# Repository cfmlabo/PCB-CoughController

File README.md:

# カフコントローラ用基板

- カフスイッチ(Switch + LED)最大５+２個  
  - J9は予備(SW6, SW7)なので実装しなくてよい
- オーディオリレー  
  - APSでは使用しないので実装しなくてよい
- GPIO(IN 8/OUT 8)  

[BOM](./BOM.md)

## CPI-DIO対応表

### Board1 / IN

| ピン番号 | 機能 |
| -- | -- |
| 1 | NC |
| 2 | SW 7 |
| 3 | SW 6 |
| 4 | SW 5 |
| 5 | SW 4 |
| 6 | SW 3 |
| 7 | SW 2 |
| 8 | SW 1 |

### Board1 / OUT

| ピン番号 | 機能 |
| -- | -- |
| 1 | リレー |
| 2 | SW 7 |
| 3 | SW 6 |
| 4 | SW 5 |
| 5 | SW 4 |
| 6 | SW 3 |
| 7 | SW 2 |
| 8 | SW 1 |

### Board2 / IN

| ピン番号 | 機能 |
| -- | -- |
| 1 | IN 8 |
| 2 | IN 7 |
| 3 | IN 6 |
| 4 | IN 5 |
| 5 | IN 4 |
| 6 | IN 3 |
| 7 | IN 2 |
| 8 | IN 1 |

### Board2 / OUT

| ピン番号 | 機能 |
| -- | -- |
| 1 | OUT 8 |
| 2 | OUT 7 |
| 3 | OUT 6 |
| 4 | OUT 5 |
| 5 | OUT 4 |
| 6 | OUT 3 |
| 7 | OUT 2 |
| 8 | OUT 1 |

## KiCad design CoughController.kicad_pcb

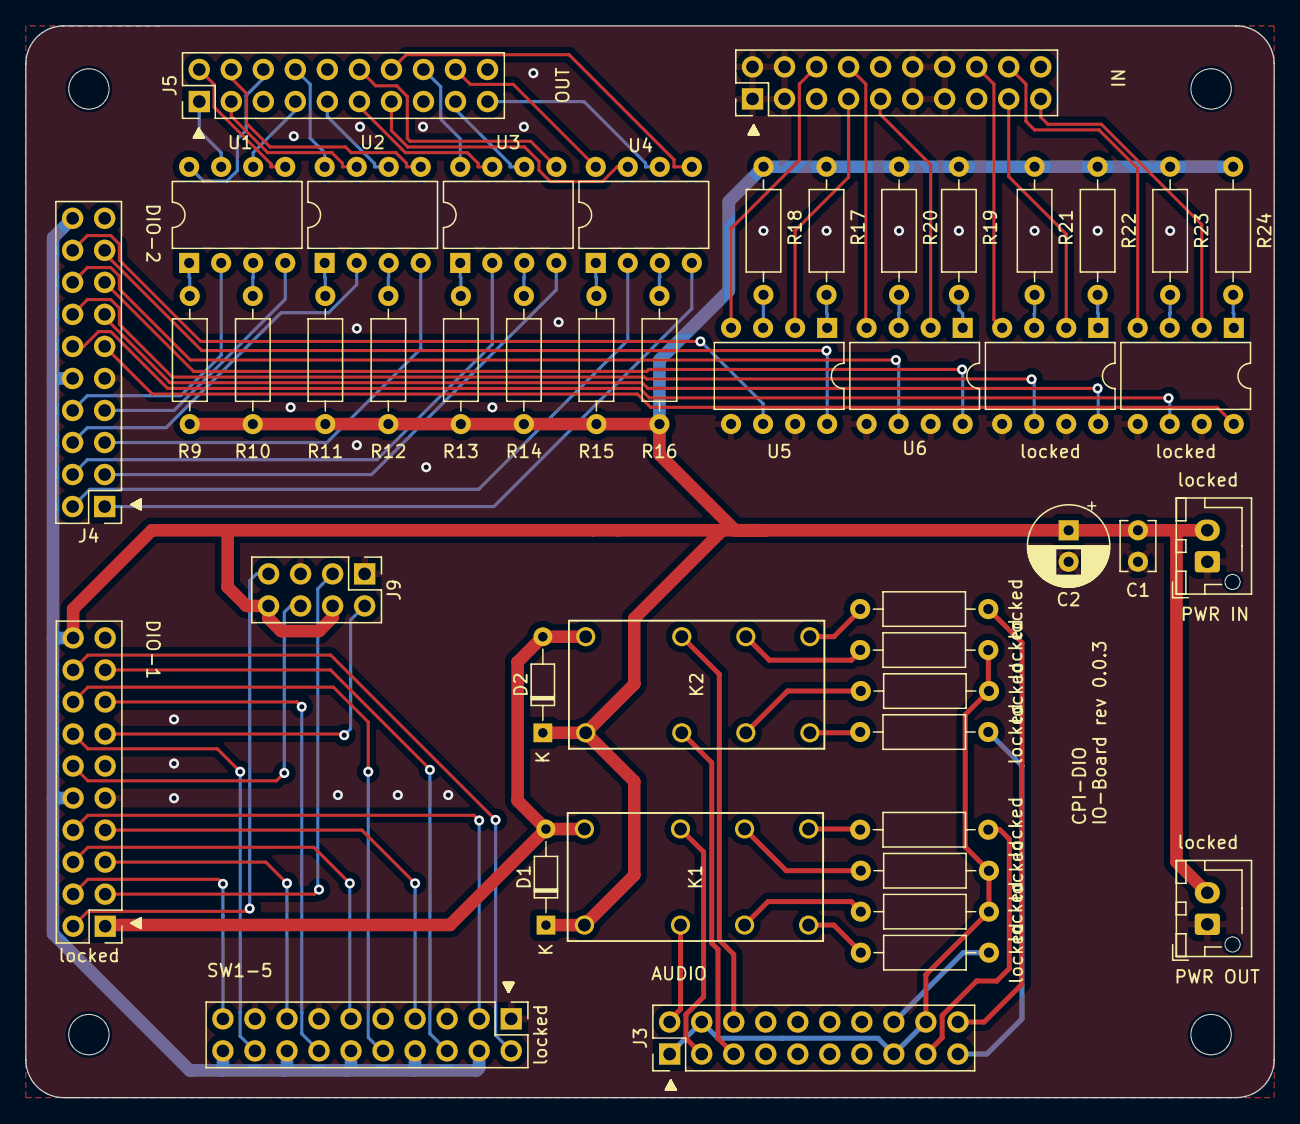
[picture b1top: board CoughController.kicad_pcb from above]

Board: 2 copper layers, 99.0 x 85.0 mm, 51 parts (0 on the bottom side), 90 nets.

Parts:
C1: 0.1uF; C_Disc_D3.8mm_W2.6mm_P2.50mm
C2: 100uF/25V; CP_Radial_D6.3mm_P2.50mm
D1, D2: 1S1588; D_DO-34_SOD68_P7.62mm_Horizontal
H1, H2, H3, H4: MountingHole; MountingHole_3.2mm_M3
J3: AUDIO IN/OUT; BoxHeader_2x10_P2.54mm_Vertical
J4: DIO-2; BoxHeader_2x10_P2.54mm_Vertical
J5: GPIO-OUT; BoxHeader_2x10_P2.54mm_Vertical
J6: GPIO-IN; BoxHeader_2x10_P2.54mm_Vertical
J9: Conn_02x04_Odd_Even; PinHeader_2x04_P2.54mm_Vertical
K1, K2: G6A-274P-DC5; RELAY_G6A-274P-DC5
R9, R10, R11, R12, R13, R14, R15, R16, R17, R18, R19, R20, R21, R22, R23, R24: 510; R_Axial_DIN0207_L6.3mm_D2.5mm_P10.16mm_Horizontal
U1, U2, U3, U4, U5, U6: TLP627-2; DIP-8_W7.62mm
locked: SW1-5; BoxHeader_2x10_P2.54mm_Vertical
locked#2, locked#7: TLP627-2; DIP-8_W7.62mm
locked#3, locked#4, locked#9, locked#10: 10K; R_Axial_DIN0207_L6.3mm_D2.5mm_P10.16mm_Horizontal
locked#5, locked#12, locked#13, locked#14: 220; R_Axial_DIN0207_L6.3mm_D2.5mm_P10.16mm_Horizontal
locked#6: DIO-1; BoxHeader_2x10_P2.54mm_Vertical
locked#8: PWR_IN; JST_XH_B2B-XH-AM_1x02_P2.50mm_Vertical
locked#11: PWR_OUT; JST_XH_B2B-XH-AM_1x02_P2.50mm_Vertical

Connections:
AUDIO-IN-L-COLD: J3.3, K1.13
AUDIO-IN-L-GND: J3.1, J3.4, J3.15, J3.18, locked#3.2, locked#4.2, locked#9.1, locked#10.1
AUDIO-IN-L-HOT: J3.2, K1.4
AUDIO-IN-R-COLD: J3.6, K2.13
AUDIO-IN-R-HOT: J3.5, K2.4
AUDIO-OUT-L-COLD: J3.17, locked#14.1
AUDIO-OUT-L-HOT: J3.16, locked#13.2
AUDIO-OUT-R-COLD: J3.20, locked#5.2
AUDIO-OUT-R-HOT: J3.19, locked#12.1
COM0: C1.1, C2.1, D1.1 (K), D2.1 (K), J4.10, J4.20, J9.4, J9.8, K1.1, K2.1, R9.2, R10.2, R11.2, R12.2, R13.2, R14.2, R15.2, R16.2, R17.2, R18.2, R19.2, R20.2, R21.2, R22.2, R23.2, R24.2, locked.4, locked.8, locked.12, locked.16, locked.20, locked#6.10, locked#6.20, locked#8.2, locked#11.2
DIO-2/IN1: J4.18, U5.6
DIO-2/IN2: J4.17, U5.8
DIO-2/IN3: J4.16, U6.6
DIO-2/IN4: J4.15, U6.8
DIO-2/IN5: J4.14, locked#7.6
DIO-2/IN6: J4.13, locked#7.8
DIO-2/IN7: J4.12, locked#2.6
DIO-2/IN8: J4.11, locked#2.8
DIO-2/OUT1: J4.8, U1.2
DIO-2/OUT2: J4.7, U1.4
DIO-2/OUT3: J4.6, U2.2
DIO-2/OUT4: J4.5, U2.4
DIO-2/OUT5: J4.4, U3.2
DIO-2/OUT6: J4.3, U3.4
DIO-2/OUT7: J4.2, U4.2
DIO-2/OUT8: J4.1, U4.4
GND: C1.2, C2.2, J4.9, J6.1, J6.2, J6.3, J6.4, J6.11, J6.12, J6.13, J6.14, J9.1, J9.5, U5.5, U5.7, U6.5, U6.7, locked.1, locked.5, locked.9, locked.13, locked.17, locked#2.5, locked#2.7, locked#6.9, locked#7.5, locked#7.7, locked#8.1, locked#11.1
GPIO-IN/1P: J6.6, U5.4
GPIO-IN/2P: J6.7, U5.2
GPIO-IN/3P: J6.8, U6.4
GPIO-IN/4P: J6.9, U6.2
GPIO-IN/5P: J6.16, locked#7.4
GPIO-IN/6P: J6.17, locked#7.2
GPIO-IN/7P: J6.18, locked#2.4
GPIO-IN/8P: J6.19, locked#2.2
GPIO-OUT/1M: J5.1, U1.7
GPIO-OUT/1P: J5.6, U1.8
GPIO-OUT/2M: J5.2, U1.5
GPIO-OUT/2P: J5.7, U1.6
GPIO-OUT/3M: J5.3, U2.7
GPIO-OUT/3P: J5.8, U2.8
GPIO-OUT/4M: J5.4, U2.5
GPIO-OUT/4P: J5.9, U2.6
GPIO-OUT/5M: J5.11, U3.7
GPIO-OUT/5P: J5.16, U3.8
GPIO-OUT/6M: J5.12, U3.5
GPIO-OUT/6P: J5.17, U3.6
GPIO-OUT/7M: J5.13, U4.7
GPIO-OUT/7P: J5.18, U4.8
GPIO-OUT/8M: J5.14, U4.5
GPIO-OUT/8P: J5.19, U4.6
unnamed: K1.6, locked#9.2
unnamed: K1.8, locked#13.1
unnamed: K1.9, locked#14.2
unnamed: K1.11, locked#3.1
unnamed: K2.6, locked#10.2
unnamed: K2.8, locked#12.2
unnamed: K2.9, locked#5.1
unnamed: K2.11, locked#4.1
unnamed: R9.1, U1.1
unnamed: R10.1, U1.3
unnamed: R11.1, U2.1
unnamed: R12.1, U2.3
unnamed: R13.1, U3.1
unnamed: R14.1, U3.3
unnamed: R15.1, U4.1
unnamed: R16.1, U4.3
unnamed: R17.1, U5.1
unnamed: R18.1, U5.3
unnamed: R19.1, U6.1
unnamed: R20.1, U6.3
unnamed: R21.1, locked#7.3
unnamed: R22.1, locked#7.1
unnamed: R23.1, locked#2.3
unnamed: R24.1, locked#2.1
RY_POW: D1.2 (A), D2.2 (A), K1.16, K2.16, locked#6.1
SW1/L1: locked.3, locked#6.8
SW1/O: locked.2, locked#6.18
SW2/L1: locked.7, locked#6.7
SW2/O: locked.6, locked#6.17
SW3/L1: locked.11, locked#6.6
SW3/O: locked.10, locked#6.16
SW4/L1: locked.15, locked#6.5
SW4/O: locked.14, locked#6.15
SW5/L1: locked.19, locked#6.4
SW5/O: locked.18, locked#6.14
SW6/L1: J9.3, locked#6.3
SW6/O: J9.2, locked#6.13
SW7/L1: J9.7, locked#6.2
SW7/O: J9.6, locked#6.12

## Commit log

2024-03-13 init
2024-03-14 カフコントローラ
2024-03-14 コネクタをピンヘッダに変更
2024-03-14 基板サイズ調整
2024-03-14 ルーティング見直し
2024-03-15 端子をピンヘッダ2x10に変更
2024-03-28 add README
2024-03-29 電源コネクタ フットプリント間違いを修正
2024-03-29 リレーのフットプリントが間違っていたのを修正
    ピン配置が間違っていた
2024-03-29 GPIO OUT ジックミスを修正
    電流シンクに変更
2024-03-29 オーディオ線強化
2024-04-03 リレー ロジックミス修正
2024-04-04 AUDIO ソケット位置調整
    ソケットピンヘッダが干渉するので移動
2024-04-08 SW6/SW7を追加
2024-04-08 リファクタリング
2024-04-08 bugfix GPIO/IN ドライ接点へ修正
    GPIO/INはドライ接点
2024-04-16 rename Symbol and Footprint of relay.
2024-04-16 fix footprint of relay
2024-04-30 add table of pin function
2024-10-08 README更新
